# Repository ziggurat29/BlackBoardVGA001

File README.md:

# BlackBoardVGA001
This is an experiment in making a DMA-based VGA output using an STM32F4VE 'black board'.

[https://os.mbed.com/users/hudakz/code/STM32F407VET6_Hello/shortlog/](https://os.mbed.com/users/hudakz/code/STM32F407VET6_Hello/shortlog/ "Info on STM32F4VE board")

This is a work-in-progress.  At this time:

- SDIO and FatFS
- USB CDC
- 'monitor' task
- LEDs
- SPI1 configured for external flash; no interface code, though

lalalililulu

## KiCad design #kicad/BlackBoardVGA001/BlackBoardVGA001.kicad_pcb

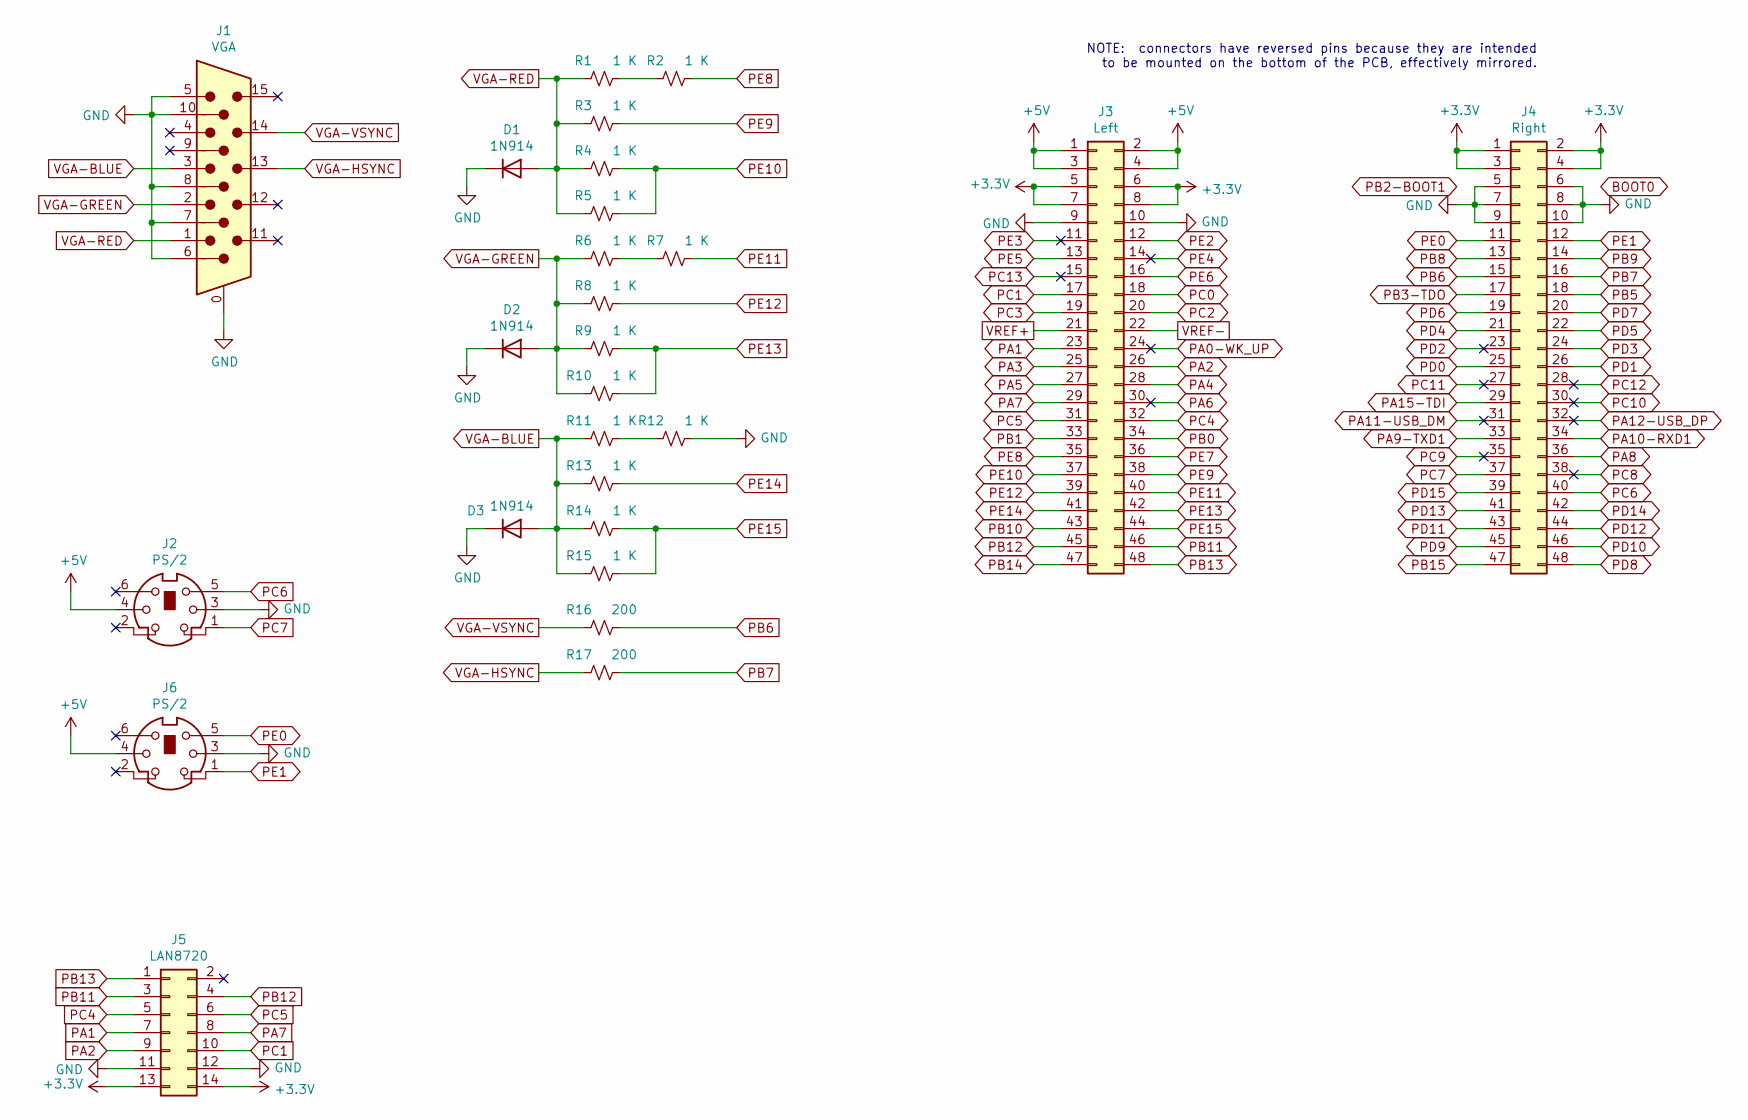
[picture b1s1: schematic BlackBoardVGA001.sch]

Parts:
D1, D2, D3: 1N914; D_DO-35_SOD27_P7.62mm_Horizontal
J1: VGA; DSUB-15-HD_Female_Horizontal_P2.29x1.98mm_EdgePinOffset8.35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
J2, J6: PS/2; Mini_din6
J3: Left; PinSocket_2x24_P2.54mm_Vertical
J4: Right; PinSocket_2x24_P2.54mm_Vertical
J5: LAN8720; PinSocket_2x07_P2.54mm_Horizontal
R1, R2, R3, R4, R5, R6, R7, R8, R9, R10, R11, R12, R13, R14, R15: 1 K; R_Axial_DIN0207_L6.3mm_D2.5mm_P2.54mm_Vertical
R16, R17: 200; R_Axial_DIN0207_L6.3mm_D2.5mm_P2.54mm_Vertical

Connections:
+3V3: J3.5, J3.6, J3.7, J3.8, J4.1, J4.2, J4.3, J4.4, J5.13, J5.14
+5V: J2.4, J3.1, J3.2, J3.3, J3.4, J6.4
GND: D1.1 (K), D2.1 (K), D3.1 (K), J1.0, J1.5, J1.6, J1.7, J1.8, J1.10, J2.3, J2.GND, J3.9, J3.10, J4.5, J4.6, J4.7, J4.8, J4.9, J4.10, J5.11, J5.12, J6.3, J6.GND, R12.2; also elsewhere on the board
unnamed: R1.2, R2.1
unnamed: R6.2, R7.1
unnamed: R11.2, R12.1
PA0-WK_UP: J3.24
PA1: J3.23, J5.7
PA2: J3.26, J5.9
PA3: J3.25
PA4: J3.28
PA5: J3.27
PA6: J3.30
PA7: J3.29, J5.8
PA8: J4.36
PA9-TXD1: J4.33
PA10-RXD1: J4.34
PA11-USB_DM: J4.31
PA12-USB_DP: J4.32
PA15-TDI: J4.29
PB0: J3.34
PB1: J3.33
PB3-TDO: J4.17
PB5: J4.18
PB6: J4.15, R16.2
PB7: J4.16, R17.2
PB8: J4.13
PB9: J4.14
PB10: J3.43
PB11: J3.46, J5.3
PB12: J3.45, J5.4
PB13: J3.48, J5.1
PB14: J3.47
PB15: J4.47
PC0: J3.18
PC1: J3.17, J5.10
PC2: J3.20
PC3: J3.19
PC4: J3.32, J5.5
PC5: J3.31, J5.6
PC6: J2.5, J4.40
PC7: J2.1, J4.37
PC8: J4.38
PC9: J4.35
PC10: J4.30
PC11: J4.27
PC12: J4.28
PC13: J3.15
PD0: J4.25
PD1: J4.26
PD2: J4.23
PD3: J4.24
PD4: J4.21
PD5: J4.22
PD6: J4.19
PD7: J4.20
PD8: J4.48
PD9: J4.45
PD10: J4.46
PD11: J4.43
PD12: J4.44
PD13: J4.41
PD14: J4.42
PD15: J4.39
PE0: J4.11, J6.5
PE1: J4.12, J6.1
PE2: J3.12
PE3: J3.11
PE4: J3.14
PE5: J3.13
PE6: J3.16
PE7: J3.36
PE8: J3.35, R2.2
PE9: J3.38, R3.2
PE10: J3.37, R4.2, R5.2
PE11: J3.40, R7.2
PE12: J3.39, R8.2
PE13: J3.42, R9.2, R10.2
PE14: J3.41, R13.2
PE15: J3.44, R14.2, R15.2
VGA-BLUE: D3.2 (A), J1.3, R11.1, R13.1, R14.1, R15.1
VGA-GREEN: D2.2 (A), J1.2, R6.1, R8.1, R9.1, R10.1
VGA-HSYNC: J1.13, R17.1
VGA-RED: D1.2 (A), J1.1, R1.1, R3.1, R4.1, R5.1
VGA-VSYNC: J1.14, R16.1
VREF+: J3.21
VREF-: J3.22

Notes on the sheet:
NOTE: connectors have reversed pins because they are intended to be mounted on the bottom of the PCB, effectively mirrored.

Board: 2 copper layers, 30 parts (0 on the bottom side), 34 nets, no tracks yet.

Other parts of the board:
REF01, REF02, REF03, REF04: MountingHole_3.2mm_M3_DIN965_Pad

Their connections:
GND: REF01.1, REF02.1, REF03.1, REF04.1; also elsewhere on the board

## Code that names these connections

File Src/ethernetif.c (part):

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    __HAL_RCC_GPIOA_CLK_ENABLE();
    __HAL_RCC_GPIOB_CLK_ENABLE();
    /**ETH GPIO Configuration    
    PC1     ------> ETH_MDC
    PA1     ------> ETH_REF_CLK
    PA2     ------> ETH_MDIO
    PA7     ------> ETH_CRS_DV
    PC4     ------> ETH_RXD0
    PC5     ------> ETH_RXD1
    PB11     ------> ETH_TX_EN
    PB12     ------> ETH_TXD0
    PB13     ------> ETH_TXD1 
    */
    GPIO_InitStruct.Pin = GPIO_PIN_1|GPIO_PIN_4|GPIO_PIN_5;
    GPIO_InitStruct.Mode = GPIO_MODE_AF_PP;
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    __HAL_RCC_ETH_CLK_DISABLE();
  
    /**ETH GPIO Configuration    
    PC1     ------> ETH_MDC
    PA1     ------> ETH_REF_CLK
    PA2     ------> ETH_MDIO
    PA7     ------> ETH_CRS_DV
    PC4     ------> ETH_RXD0
    PC5     ------> ETH_RXD1
    PB11     ------> ETH_TX_EN
    PB12     ------> ETH_TXD0
    PB13     ------> ETH_TXD1 
    */
    HAL_GPIO_DeInit(GPIOC, GPIO_PIN_1|GPIO_PIN_4|GPIO_PIN_5);

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
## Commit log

2020-06-15 initial chicken. USB CDC, uart1, sdio fatfs, leds, declare ram sections.
2020-06-17 get SDIO working again, again
2020-06-18 add PS/2 gpio defs
2020-06-19 support battery-backed RTC
2020-06-19 added battery-backed BKSRAM support
2020-06-19 update notes about what wacky hacks were added for rtc
2020-06-19 needed to init the RTC_TimeTypeDef struct to avoid random DST issues when setting time.
2020-06-20 added DAC1 and DAC2; not wired to anything, though
2020-06-22 setup HSYNC via TIM4 ch1 pwm, and interrupt for video state machine
2020-06-23 starting to make the video module. it's just a stub at the moment.
2020-06-24 TIM1 will become the pixel clock; this is initial testing of the clock output
2020-06-24 use output compares on TIM4 to drive various phases of video generation
2020-06-24 TIM1 is a slave in 'gated' mode to TIM4,OC2. This is intended to clock DMA transfers for video out. However, the polarity is opposite of what I want and I haven't figured it out yet.
2020-06-25 after much yanking and twisting, the triggered slave mode for the pixel clock is working correctly. The two most significant factors were a) realizing that you must force the TIM4 OC2 (used as the tr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
2020-06-25 vsync state machine and minor tidiness
2020-06-28 DMA of pixel data is working, but the max resolution I currently can get is about 600 horz. Anyway, it's time to pull out the scaffolding code and put it in some 'video' modules for further tinkering.
2020-06-28 moved existing video experiments out to the 'video' module for further tinkering
2020-06-28 changed from HAL to LL libs for many (though not all) things. mainly the video stuff.
2020-06-28 raise priority of end-of-scan-line interrupt to highest (must not call freertos). clean a few LL gpio things; wire back in the EXTI handlers.
2020-06-29 move RTC to the LL libs; there seems to be a problem with resetting the clock on every boot now, though
2020-06-29 fix issues with LL rtc generate code that always resets the rtc on each boot
2020-06-30 move USART1 to the LL libs
2020-07-01 added LwIP and ETH via CubeMX; untested
2020-07-01 extended 'diag' to show memory regions and usage
2020-07-04 added heapwalk to get more detailed heap usage stats (and corrected minor bug in heapwalk -- misnamed parameter)
2020-07-04 heapwalk was wildly broken (and overcomplicated)
2020-07-04 (reflect heap fixes into '#fixups')
2020-07-04 added heap walk output for first 20 allocs, which should be enough
2020-07-04 add diagnostics for the TCPIP and ETHERNET threads
2020-07-04 add eth/tcpip info to 'diag' (ip, netmask, gateway)
2020-07-05 added board design; schematic and layout (not routed)
2020-07-05 added a second ps2 connector, eventually for mouse (not connected to any gpio yet)
2020-07-07 closed board outline polygon; added mounting holes and DIN shield to GND net
2020-07-07 moved VGA connector to other end of board
2020-07-07 using E0 and E1 for second PS/2
2020-07-09 modified page parameters (title block fields; paper size)
2020-07-09 swap position of LAN8720 and VGA
2020-07-09 add a project-specific symbol library; create a schematic symbol for the PAM8403 amplifier breakout board module

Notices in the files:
Src/ethernetif.c:
© Copyright (c) 2020 STMicroelectronics.
All rights reserved.
This software component is licensed by ST under Ultimate Liberty license
(C) COPYRIGHT STMicroelectronics *****END OF FILE
